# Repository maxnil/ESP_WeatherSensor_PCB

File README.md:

# ESP_WeatherStation_PCB
Simple weather station (temperature, humidity and air pressure) based around a ESP8266 module

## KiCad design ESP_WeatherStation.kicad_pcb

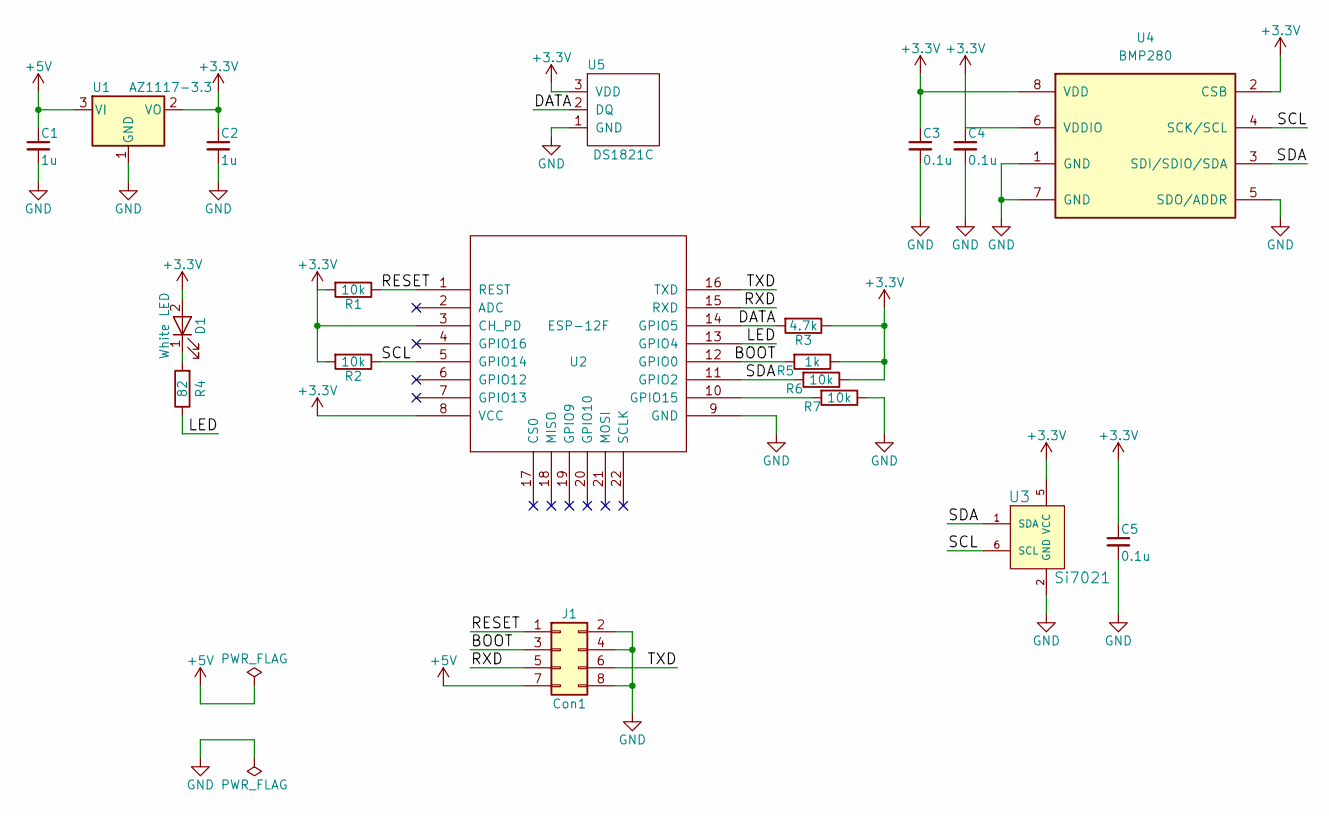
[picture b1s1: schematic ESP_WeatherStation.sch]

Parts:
C1, C2: 1u; C_0603
C3, C4, C5: 0.1u; C_0603
D1: White LED; LED_0603
J1: Con1; Pin_Header_Straight_2x04_Pitch2.54mm_SMD
R1, R2, R6, R7: 10k; R_0603
R3: 4.7k; R_0603
R4: 82; R_0603
R5: 1k; R_0603
U1: AZ1117-3.3; SOT-223
U2: ESP-12F; ESP-12E_SMD
U3: Si7021; DFN-6-1EP_3x3mm_Pitch0.95mm
U4: BMP280; BOSCH_BMP280; MPN BMP280
U5: DS1821C; TO-92_Inline_Narrow_Oval

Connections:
+3V3: C2.1, C3.1, C4.1, C5.1, D1.2 (A), R1.2, R2.2, R3.1, R5.1, R6.1, U1.2 (VO), U2.3 (CH_PD), U2.8 (VCC), U3.5 (VCC), U4.2 (CSB), U4.6 (VDDIO), U4.8 (VDD), U5.3 (VDD)
+5V: C1.1, J1.7, U1.3 (VI)
/BOOT: J1.3, R5.2, U2.12 (GPIO0)
/DATA: R3.2, U2.14 (GPIO5), U5.2 (DQ)
/LED: R4.1, U2.13 (GPIO4)
/RESET: J1.1, R1.1, U2.1 (REST)
/RXD: J1.5, U2.15 (RXD)
/SCL: R2.1, U2.5 (GPIO14), U3.6 (SCL), U4.4 (SCK/SCL)
/SDA: R6.2, U2.11 (GPIO2), U3.1 (SDA), U4.3 (SDI/SDIO/SDA)
/TXD: J1.6, U2.16 (TXD)
GND: C1.2, C2.2, C3.2, C4.2, C5.2, J1.2, J1.4, J1.8, R7.1, U1.1 (GND), U2.9 (GND), U3.2 (GND), U4.1 (GND), U4.5 (SDO/ADDR), U4.7 (GND), U5.1 (GND)
unnamed: D1.1 (K), R4.2
unnamed: R7.2, U2.10 (GPIO15)

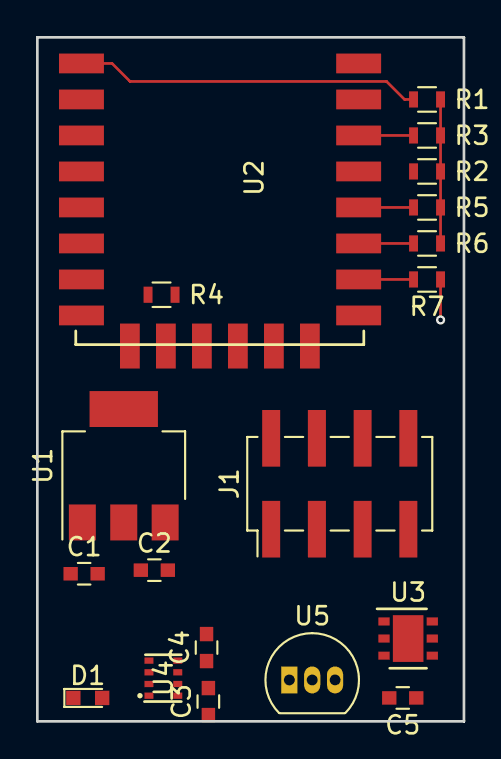
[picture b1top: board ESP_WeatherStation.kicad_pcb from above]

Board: 2 copper layers, 23.7 x 38.0 mm, 19 parts (0 on the bottom side), 13 nets.

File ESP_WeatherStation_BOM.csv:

"Source:","/Users/max/Documents/KiCad/Projects/ESP_WeatherStation/ESP_WeatherStation.sch"
"Date:","2018 March 17, Saturday 00:23:12"
"Tool:","Eeschema 4.0.7"
"Generator:","/Applications/Kicad/kicad.app/Contents/SharedSupport/plugins/bom_csv_grouped_by_value.py"
"Component Count:","19"

"Individual Components:"

"Item","Qty","Reference(s)","Value","LibPart","Footprint","Datasheet","BOM","MPN","Manuf"
"","","C1","1u","device:C_Small","Capacitors_SMD:C_0603","","","",""
"","","C2","1u","device:C_Small","Capacitors_SMD:C_0603","","","",""
"","","C3","0.1u","device:C_Small","Capacitors_SMD:C_0603","","","",""
"","","C4","0.1u","device:C_Small","Capacitors_SMD:C_0603","","","",""
"","","C5","0.1u","device:C_Small","Capacitors_SMD:C_0603","","","",""
"","","D1","White LED","device:LED","LEDs:LED_0603","","","",""
"","","J1","Con1","ESP_WeatherStation-cache:Conn_02x04_Odd_Even","Pin_Headers:Pin_Header_Straight_2x04_Pitch2.54mm_SMD","","","",""
"","","R1","10k","device:R","Resistors_SMD:R_0603","","","",""
"","","R2","4.7k","device:R","Resistors_SMD:R_0603","","","",""
"","","R3","82","device:R","Resistors_SMD:R_0603","","","",""
"","","R4","1k","device:R","Resistors_SMD:R_0603","","","",""
"","","R5","10k","device:R","Resistors_SMD:R_0603","","","",""
"","","R6","10k","device:R","Resistors_SMD:R_0603","","","",""
"","","R7","10k","device:R","Resistors_SMD:R_0603","","","",""
"","","U1","AZ1117-3.3","ESP_WeatherStation-cache:AZ1117-3.3","TO_SOT_Packages_SMD:SOT-223","","","",""
"","","U2","ESP-12F","ESP8266:ESP-12F","ESP8266:ESP-12E_SMD","","","",""
"","","U3","Si7021","MaxNil_components:Si7021","Housings_DFN_QFN:DFN-6-1EP_3x3mm_Pitch0.95mm","","","",""
"","","U4","BMP280","MaxNil_components:BMP280","MaxNil:BOSCH_BMP280","https://ae-bst.resource.bosch.com/media/_tech/media/datashee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","Bosch BMP280","BMP280","Bosch"
"","","U5","DS1821C","maxim:DS1821C","TO_SOT_Packages_THT:TO-92_Inline_Narrow_Oval","","","",""



"Collated Components:"

"Item","Qty","Reference(s)","Value","LibPart","Footprint","Datasheet","BOM","MPN","Manuf"
"1","2","C1, C2","1u","device:C_Small","Capacitors_SMD:C_0603","","","",""
"2","3","C3, C4, C5","0.1u","device:C_Small","Capacitors_SMD:C_0603","","","",""
"3","1","D1","White LED","device:LED","LEDs:LED_0603","","","",""
"4","1","J1","Con1","ESP_WeatherStation-cache:Conn_02x04_Odd_Even","Pin_Headers:Pin_Header_Straight_2x04_Pitch2.54mm_SMD","","","",""
"5","4","R1, R5, R6, R7","10k","device:R","Resistors_SMD:R_0603","","","",""
"6","1","R2","4.7k","device:R","Resistors_SMD:R_0603","","","",""
"7","1","R3","82","device:R","Resistors_SMD:R_0603","","","",""
"8","1","R4","1k","device:R","Resistors_SMD:R_0603","","","",""
"9","1","U1","AZ1117-3.3","ESP_WeatherStation-cache:AZ1117-3.3","TO_SOT_Packages_SMD:SOT-223","","","",""
"10","1","U2","ESP-12F","ESP8266:ESP-12F","ESP8266:ESP-12E_SMD","","","",""
"11","1","U3","Si7021","MaxNil_components:Si7021","Housings_DFN_QFN:DFN-6-1EP_3x3mm_Pitch0.95mm","","","",""
"12","1","U4","BMP280","MaxNil_components:BMP280","MaxNil:BOSCH_BMP280","https://ae-bst.resource.bosch.com/media/_tech/media/datashee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","Bosch BMP280","BMP280","Bosch"
"13","1","U5","DS1821C","maxim:DS1821C","TO_SOT_Packages_THT:TO-92_Inline_Narrow_Oval","","","",""

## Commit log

2018-03-07 First version
2018-03-13 Final version
2018-03-13 Hepp
2018-04-22 Full BOM
2018-04-22 BOM .csv file
